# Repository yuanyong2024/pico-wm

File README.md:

# Introduction
As a hardware engineer, it's always have difficulties to coding in python than C.Plus,I'm a fan of Raspberry Pi's hardware. So when they release the pico w and when i saw the schematic for it. 
I was thinking well I should build one module based on that architecture with below several reasons
1. Keep motivated on learn circuitpython.
2. Learn how to design a compact module.
3. improve the skill of tuning the antenna.
4. gain more on how to design a product.
5. I name it pico wm (pico w means its a variant of official Raspberry Pi pico w and m means it's a module)
So there is. I made it work even at the first verison. And optimized a little bit on v0.0.2. Probably there is a v0.0.3 if I find out something that need to get improved.

# Features:
1. use the same wifi chip(infineon CY43439) and circuitry like pico w. So wirelss function api is exactly the same(not like most of the rp2040+esp solution on market)
2. Flash size is the same like pico w (16Mb)
3. 6 layer board design with a complete ground on bottom layer. Improved the signal integraty. But also increased the costs -:(
4. compact size(28.5x17.5mm), so that it can be suitable for most of the situation.
5. All the GPIO had been exposed at the bottom side in a LGA footprint.
6. 50ohm impedance achieved for the RF trace.
7. onboard WiFi/BLE antenna.But obviously not as good as official pico w for now -:(
8. Reserved for a top shield cover feature.
9. all  the vias on the pcb is filled plating.
10. optimize the power topology, make it easier to design the carrier board based on this module.
11. Ofcourse totally open-sourced.

# Limitations:
1. The only limitation for this module would be the RF performance, Still need more time to tuning it.
2. And because I need to make sure the module is functioning well after SMT, so I didnot populate the shield cover yet.

# considering support me?
Building the module definitley take time and energy.
And also it's cost a lot. As the module itself is a six layer board and I'm using the expensive Infineon chip. So I would appreciate anyone who can support me by purchase it from [this link](https://www.elecrow.com/pico-wm.html)

# Attentions:
1. This is just a module. So need customer build a carrier board for it.
2. Those who interested in this module can use the picoduino as a start point and use the pico w m schematic and pcb lib from that picoduino open source file.
3. I will also build a feather compatible one later.

# useful links:
[pico w datasheet](https://datasheets.raspberrypi.com/picow/pico-w-datasheet.pdf?_gl=1*pez2dw*_ga*NTM5ODUxMTkxLjE3MTE2MzI0NTI.*_ga_22FD70LWDS*MTcxMTYzMjQ1Mi4xLjAuMTcxMTYzMjQ1Mi4wLjAuMA..)

[raspberry pi pico documentation](https://www.raspberrypi.com/documentation/microcontrollers/raspberry-pi-pico.html#raspberry-pi-pico-w)

[picoduino design file](https://github.com/yuanyong2024/picoduino)

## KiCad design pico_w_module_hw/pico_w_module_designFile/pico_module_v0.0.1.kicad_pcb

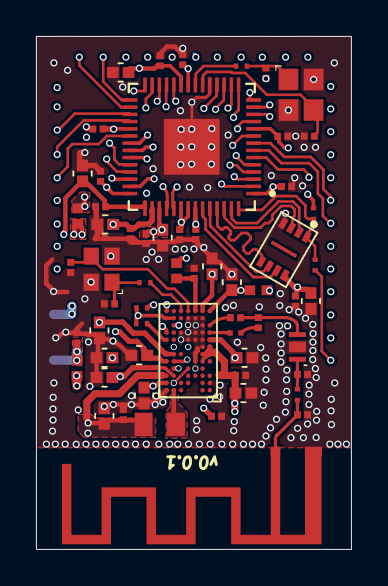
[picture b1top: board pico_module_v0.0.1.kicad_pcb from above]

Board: 6 copper layers, 17.5 x 28.5 mm, 61 parts (0 on the bottom side), 70 nets.

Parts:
ANT1: U.FL-R-SMT-1(10); AN043_2.4GHZ
C1, C2, C3, C4, C5, C6, C7, C9, C11, C22, C23, C25, C26, C30, C40: C0402 12pF 50V; C0402
C8, C10, C20, C21, C31: C0402 12pF 50V; C0201
C12, C13, C14, C15, C16, C17, C18, C19, C24, C27, C28, C29, C32, C33, C34, C35, C36, C37, C38, C39: C0201 DNP; C0201
FB1, FB2, FB3: Ferrite 33Ohm 6A; L0402
L1: Inductor 6.8uH 30%; L0805
L2: L0603 470nH 1.4A; l0201
Q1: 37.4MHz; Q22FA12800078
Q2: 12MHz; 2520
R1, R2, R4, R5, R8, R9, R10: R0402 DO NOT PLACE; R0201
R3: R0402 1K 5% 1/16W; R0402
U1: CYW43439KUBG; CY43439
U2: LFB212G45CG7D227
U3: RP2040
U4: W25Q16JVUXIQ; USON8_3X2MM
U5: PICO_W_MODULE; PICO_M_SMT

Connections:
1.1V: C25.2, C26.2, C27.2, C28.2, C29.2, U3.23, U3.45, U3.50
ADC_REF: C23.2, C24.2, U3.43, U5.36
BOOTSEL: R9.2, U5.2
GND: ANT1.2, ANT1.3, C1.1, C2.1, C3.1, C4.1, C5.1, C6.1, C7.1, C8.1, C9.1, C10.1, C11.1, C13.1, C14.1, C16.1, C17.1, C18.1, C19.1, C20.1, C21.1, C22.1, C23.1, C24.1, C25.1, C26.1, C27.1, C28.1, C29.1, C30.1, C31.1, C32.1, C33.1, C34.1, C35.1, C36.1, C37.1, C38.1, C39.1, C40.1, Q1.2, Q1.4, Q2.2, Q2.4, U1.A7, U1.B1, U1.B6, U1.D4, U1.E3, U1.G2, U1.H2, U1.H3, U1.H4, U1.J2, U1.J3, U1.J5, U1.K2, U1.L2, U1.L3, U1.L4, U2.G, U3.19, U3.57, U4.4, U5.1, U5.15, U5.27, U5.37, U5.39, U5.41
GPIO0: U3.2, U5.3
GPIO1: U3.3, U5.4
GPIO2: U3.4, U5.5
GPIO3: U3.5, U5.6
GPIO4: U3.6, U5.7
GPIO5: U3.7, U5.8
GPIO6: U3.8, U5.9
GPIO7: U3.9, U5.10
GPIO8: U3.11, U5.11
GPIO9: U3.12, U5.12
GPIO10: U3.13, U5.13
GPIO11: U3.14, U5.14
GPIO12: U3.15, U5.16
GPIO13: U3.16, U5.17
GPIO14: U3.17, U5.18
GPIO15: U3.18, U5.19
GPIO16: U3.27, U5.23
GPIO17: U3.28, U5.24
GPIO18: U3.29, U5.25
GPIO19: U3.30, U5.26
GPIO20: U3.31, U5.30
GPIO21: U3.32, U5.31
GPIO22: U3.34, U5.32
GPIO26: U3.38, U5.33
GPIO27: U3.39, U5.34
GPIO28: U3.40, U5.35
MCU_VDD: FB3.1, U5.38
M_USB_N: U3.46, U5.29
M_USB_P: U3.47, U5.28
M_VCC: C30.2, C32.2, C33.2, C34.2, C35.2, C36.2, C37.2, C38.2, C39.2, C40.2, FB3.2, R10.2, U3.1, U3.10, U3.22, U3.33, U3.42, U3.44, U3.48, U3.49, U4.8
NetANT1_1: ANT1.1, C13.2, R4.1
NetC7_2: C7.2, R3.2, U1.H1
NetC8_2: C8.2, FB2.2, U1.M3
NetC12_1: C12.1, C15.2, U2.O
NetC12_2: C12.2, U1.K1
NetC14_2: C14.2, R4.2, U2.I
NetC15_1: C15.1, L2.1
NetC16_2: C16.2, Q1.3, U1.M4
NetC17_2: C17.2, Q1.1, R5.1
NetC18_2: C18.2, Q2.3, U3.20
NetC19_2: C19.2, Q2.1, R8.1
NetL1_1: L1.1, U1.A6
NetL2_2: L2.2, U1.J1
NetR1_2: R1.2, U1.K6
NetR2_2: R2.2, U1.H7
NetR5_2: R5.2, U1.M5
NetR8_2: R8.2, U3.21
NetU1_E6: U1.E6, U1.G6, U3.35
QSPI_SCLK: U3.52, U4.6
QSPI_SD0: U3.53, U4.5
QSPI_SD1: U3.55, U4.2
QSPI_SD2: U3.54, U4.3
QSPI_SD3: U3.51, U4.7
RF_VDD: C31.2, FB1.1, U5.40
RUN: U3.26, U5.22
SDIO_CLK: U1.M7, U3.41
SDIO_CS: U1.J7, U3.37
SDIO_DIO: R1.1, R2.1, U1.L6, U1.L7, U3.36
SWCLK: U3.24, U5.20
SWDIO: U3.25, U5.21
VDD_BAT: C11.2, C22.2, FB1.2, U1.B7, U1.F6, U1.F7
VIN_LDO: C1.2, C2.2, C20.2, L1.2, U1.C7, U1.M2
VOUT_3P3: C5.2, C6.2, R3.1, U1.E7, U1.M1
VOUT_CORE: C3.2, C10.2, U1.C6, U1.D3, U1.G4
VOUT_LN: C4.2, C9.2, C21.2, FB2.1, U1.D6, U1.E2, U1.F1, U1.F2, U1.G1
~QSPI_SS: R9.1, R10.1, U3.56, U4.1

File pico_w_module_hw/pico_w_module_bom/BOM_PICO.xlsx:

Designator | Quantity | Footprint | MFG | PN | Value
U4 | 1 | USON8_3X2MM | WINBOND | W25Q16JVUXIQ | N/A
U3 | 1 |  | Raspberrypi | RP2040 | N/A
U2 | 1 | LFB212G45CG7D227 | muRata | LFB212G45CG7D227 | N/A
U1 | 1 | CY43439 | Infineon | CYW43439KUBG | N/A
R8, R9 | 2 | R0201 | YAGEO | RC0201FR-071KL | 1K
R5 | 1 | R0201 | YAGEO | AF0201JR-07220RL | 220R
R4 | 1 | R0201 | YAGEO | RC0201FR-070RL | 0R
R3 | 1 | R0402 | YAGEO | RC0402FR-0722RL | 22R
R2 | 1 | R0201 | YAGEO | RC0201JR-0710KL | 10K
R1 | 1 | R0201 | YAGEO | RC0201DR-07470RL | 470R
Q2 | 1 | 2520 | EPSON | Q24FA20H00687 | 12MHz
Q1 | 1 | Q22FA12800078 | EPSON | Q22FA12800078 | 37.4MHz
L2 | 1 | l0201 | muRata | LQP03PN4N7J02D | 4.7nH
L1 | 1 | L0805 | TAIYO YUDEN | BRC2012T2R2MD | 2.2uH
FB1, FB2, FB3 | 3 | L0402 | muRata | BLM15AG601SN1D | 600R@100MHz
C23, C25, C26, C30, C40 | 5 | C0402 | muRata | GRM155R61A106ME44D | 10uF
C18, C19 | 2 | C0201 | muRata | GRM0335C1H150FA01D | 15pF
C16, C17 | 2 | C0201 | muRata | GRM0335C1H180JA01D | 18pF
C12, C15 | 2 | C0201 | muRata | GRM0335C1H100JA01D | 10pF
C8, C10, C20, C21, C24, C27, C28, C29, C31, C32, C33, C34, C35, C36, C37, C38, 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 | 17 | C0201 | muRata | GRM033Z71A104KE14D | 0.1uF
C1, C2, C3, C4, C5, C6, C7, C9, C11, C22 | 10 | C0402 | muRata | GRM155R61A475KEAAD | 4.7uF

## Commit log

2024-03-28 add pictures
2025-05-04 update design file
